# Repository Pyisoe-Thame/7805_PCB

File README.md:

# 7805 PCB design

This repository contains the PCB design files for a voltage regulator circuit based on the popular 7805 IC. The 7805 IC is a linear voltage regulator that provides a stable 5V output from a higher input voltage. Kicad is used to design the PCB.

The PCB has a Schottky diode for fast switching, several bypass capacitors and L7805CV IC, and last but not least, the screw terminals for universal input and output. 

The Schottky diode at the input side has maximum current rating of 1A and voltage drop of 0.45\~0.65V. The maximum output current is 1.5A; 7.5W in power. According to the datasheet, 7~35V without the aforementioned voltage drop is needed to satisfy the output. The electrolytic capacitor at the output side can be dumped as it is not found in the datasheet recommended circuit.

Note that there are other variants of 7805 IC that can only support output current of up to 1A.

## Features

- Compact Design: The PCB layout is optimized for a compact size, making it suitable for various projects where space is a constraint.
- Easy Integration: Designed with easy integration in mind, the PCB layout facilitates straightforward connection to input and output power sources and peripheral components.
- Versatile Application: Suitable for a wide range of applications requiring a regulated 5V power supply, including hobbyist electronics projects, prototyping, and small-scale production.

## Contents

- images/: The folder contains the screenshots taken by snipping tool to demonstrate the overview of what the product would look like.
- gerber files/: This directory contains the PCB design files in Gerber format, ready for fabrication.
- 7805.kicad_pcb: This is the actual PCB design file that controls the final product of the project.
- 7805.kicad_sch: Here, you'll find the schematic diagram of the voltage regulator circuit for reference.
- README.md: You're reading it right now! This file provides an overview of the project and instructions for usage.

## Screenshots

**Original Circuit Credit**:  
This project was inspired by [The Engineering Mindset](https://www.youtube.com/@EngineeringMindset)'s video titled [5V Regulator design tutorial](https://www.youtube.com/watch?v=d-j0onzzuNQ). While the original circuit served as inspiration, the PCB design in this repository is modified according to my own likeness, which I also am offering for free. Feel free to use and modify it as needed.

## License

This PCB design is provided under the [MIT](https://choosealicense.com/licenses/mit/) License, allowing for free use, modification, and distribution.

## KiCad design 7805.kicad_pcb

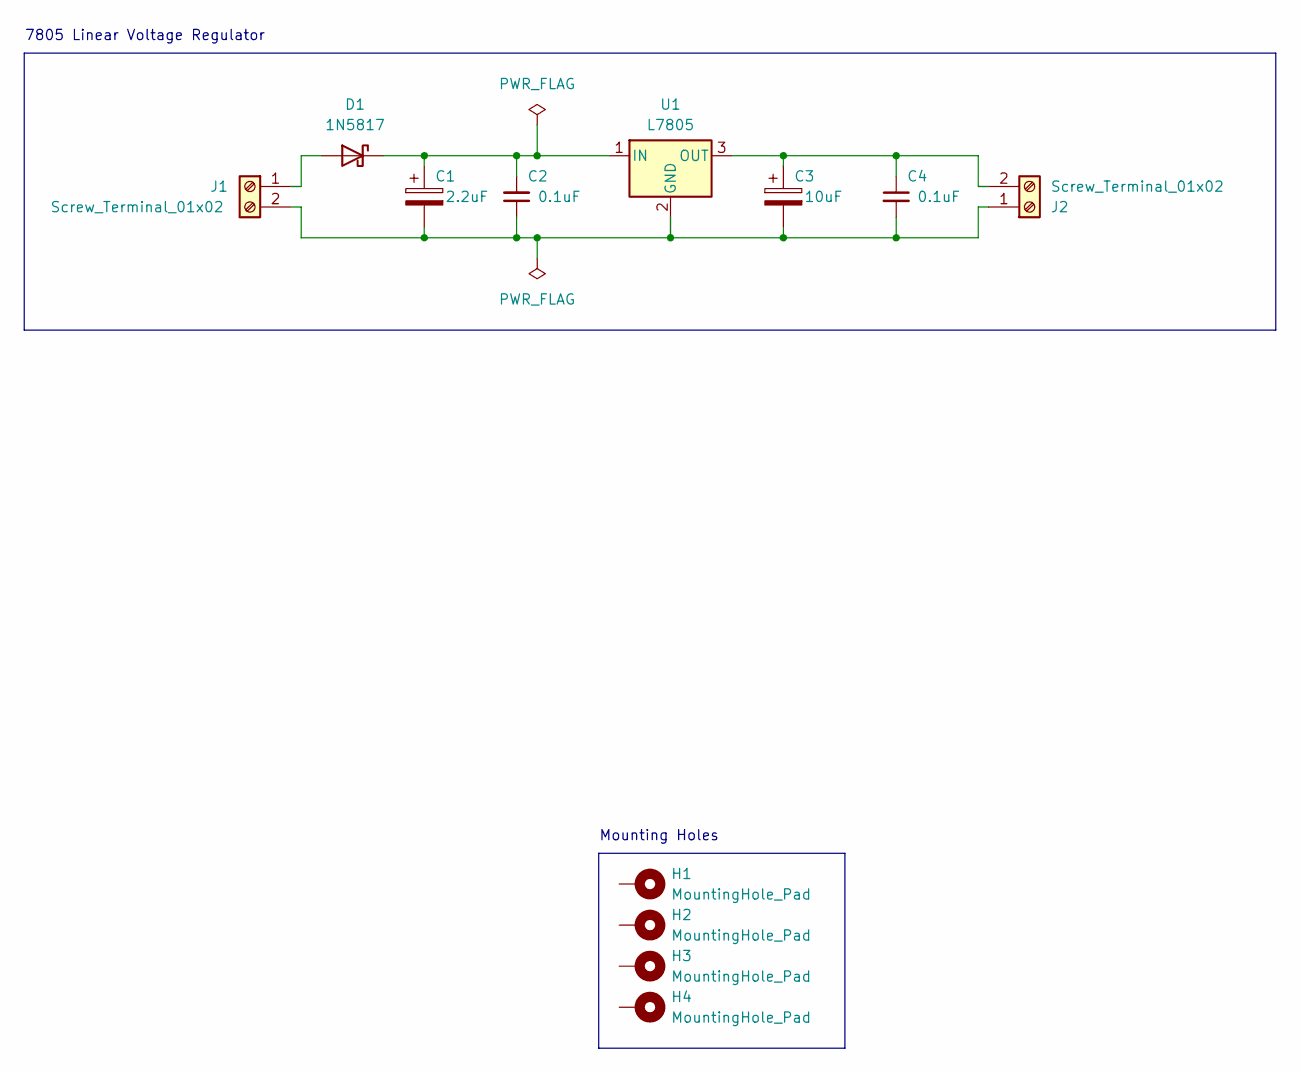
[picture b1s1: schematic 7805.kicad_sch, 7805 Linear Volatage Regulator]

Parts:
C1: 2.2uF; CP_Radial_D5.0mm_P2.50mm
C2, C4: 0.1uF; C_Disc_D9.0mm_W5.0mm_P7.50mm
C3: 10uF; CP_Radial_D5.0mm_P2.50mm
D1: 1N5817; D_DO-41_SOD81_P10.16mm_Horizontal
H1, H2, H3, H4: MountingHole_Pad; MountingHole_3.2mm_M3_Pad
J1, J2: Screw_Terminal_01x02; TerminalBlock_Phoenix_MKDS-1,5-2-5.08_1x02_P5.08mm_Horizont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
U1: L7805; TO-220-3_Horizontal_TabDown

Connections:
unnamed: D1.2 (A), J1.1
unnamed: C1.1, C2.2, D1.1 (K), U1.1 (IN)
unnamed: C1.2, C2.1, C3.2, C4.2, J1.2, J2.1, U1.2 (GND)
unnamed: C3.1, C4.1, J2.2, U1.3 (OUT)

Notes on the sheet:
Mounting Holes
7805 Linear Voltage Regulator

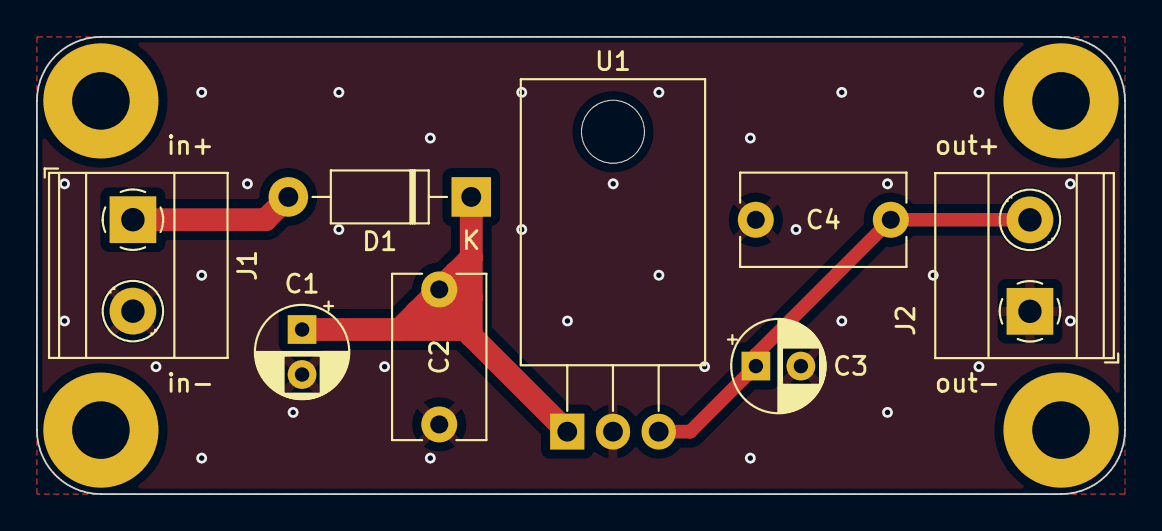
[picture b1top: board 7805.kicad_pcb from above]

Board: 2 copper layers, 60.5 x 25.4 mm, 12 parts (0 on the bottom side), 4 nets.

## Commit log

2024-02-08 readme and pictures added
2024-02-08 image links added to readme file
